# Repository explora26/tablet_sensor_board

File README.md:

# LIS3DH 三軸加速度計小板（NanoPC-T4 I2C2）

> 另一塊平板電源鍵小板在 [`power_button/`](power_button/README.md)。

板上用 LDO 轉出 3.0V，讓 I2C 電位和 NanoPC-T4 的 I2C2（3.0V I/O）一致，同時經 JST 接頭供電和 I2C 給 BQ25798 充電板。

**狀態：原理圖和 layout 完成（87.6 × 25.4 mm，雙層板），DRC 無錯誤。**

## 規格
| 項目 | 內容 |
|---|---|
| 感測器 | ST LIS3DH，LGA-16 3×3 mm |
| I2C 位址 | 0x18（SA0 接 GND），WHO_AM_I = 0x33 |
| 電源 | VIN 3.3–5.5V → TLV75530（3.0V，500 mA） |
| 上拉電阻 | SCL/SDA 各 4.7k 上拉到 3.0V（R1/R2，T4 的上拉夠用時可以不焊） |
| 介面 | J1：1×7 排針，2.54 mm，接 T4；J2：JST PH 2.0 5 pin，接 BQ25798 充電板；J3：1×10 排母，插 WL-125 RFID 模組；J4：Molex PicoBlade 1.25 mm 2 pin，接 RFID 天線 |
| 固定 | H1、H2：2 個 M3 鎖孔（3.2 mm，不鍍銅），layout 時靠近 LIS3DH 擺放，讓加速度計鎖緊固定 |

## J1 ↔ NanoPC-T4 40-pin
| J1 | 訊號 | T4 腳位 |
|---|---|---|
| 1 | VIN | Pin 2（5V） |
| 2 | GND | Pin 6 |
| 3 | SCL | Pin 5（I2C2_SCL） |
| 4 | SDA | Pin 3（I2C2_SDA） |
| 5 | INT1 | Pin 11（GPIO1_A1，3V，選用） |
| 6 | CHG_INT | Pin 7（GPIO1_A0，3V） |
| 7 | RFID_TX | Pin 21（UART4_RX，3V），需在 device tree 啟用 UART4、關閉 SPI1 |

## J2 ↔ BQ25798 充電板（JST PH 2.0，5 pin）
| J2 | 訊號 | 說明 |
|---|---|---|
| 1 | GND | |
| 2 | INT | BQ25798 的 /INT（開汲極，低電位觸發），上拉電阻在充電板上（小板不另加），經 J1 第 6 腳送到 T4 |
| 3 | I2C_SCL | 和 T4 的 I2C2 共用匯流排 |
| 4 | I2C_SDA | 同上 |
| 5 | 3V | 小板輸出的 3.0V（來自 U1），供充電板的上拉電阻和邏輯電路使用 |

I2C2 上的位址：LIS3DH 是 0x18，BQ25798 是 0x6B，沒有衝突。

## J3 ↔ WL-125 125kHz RFID 模組（1×10 排母，2.54 mm）
模組焊 10P 排針直接插上，排針從模組元件面（有 IC 的那面）焊接。模組只有 9 支腳，多出來的防呆腳在**模組第 1 腳旁邊**，所以 J3 腳位 = 模組腳位 + 1。

| J3 | 模組腳位 | 小板上的接法 |
|---|---|---|
| 1 | — | 防呆腳，不接 |
| 2 | 1 天線 1 | ANT1 → J4 第 1 腳（天線線圈），有 50–100 Vpp 諧振電壓 |
| 3 | 2 天線 2 | ANT2 → J4 第 2 腳 |
| 4 | 3 輸出模式選擇 | 接 VCC_RF（高電位 = UART 輸出，規格書規定不可懸空） |
| 5 | 4 蜂鳴器輸出 | 不接 |
| 6 | 5 TX（9600 8N1，5V TTL） | 經 Q1 BSS138 電位轉換成 3.0V（RFID_TX），送到 J1 第 7 腳 |
| 7 | 6 維根 D0 | 不接 |
| 8 | 7 /RESET（低電位有效） | R7 10k 上拉到 VCC_RF |
| 9 | 8 GND | GND |
| 10 | 9 VCC（5V） | VCC_RF：+5V 經三階 RC 濾波（見下方） |

- 電源濾波（三階 RC，依 WL-125 規格書附錄）：
  `+5V → R6 4.7Ω → C5 1000µF → R8 1Ω → C7 1000µF → R9 1Ω → C8 1000µF + C6 100nF → VCC_RF`
  - C5、C7、C8：Panasonic EEE-FT1A102AP（1000µF 10V，SMD 8 × 10.2 mm，LCSC C278408），封裝 `CP_Elec_8x10.5`；缺貨時可用 EEE-FK1A102P（C278397），但它是 10 mm，要改封裝 `CP_Elec_10x10.5`
  - R6 用 4.7Ω 限制上電湧浪電流（3000µF 從 T4 的 5V 充電，峰值約 1A）
  - 25 mA 時總壓降約 0.17V，模組約 4.8V
  - C6 補 1 MHz 以上的高頻；C8、C6 要緊貼 J3 第 10 腳
  - 1 kHz–500 kHz 約衰減 60 dB（估算值，未含走線）
- 電位轉換：Q1 BSS138 + R4/R5 各 10k 上拉（3.0V 側 / 5V 側），和 Adafruit #757 相同架構
- 卡號格式：`02` + 10 字元 ASCII 卡號 + 1 byte 校驗（XOR）+ `03`，共 13 bytes
- 規格書強調電源要乾淨：不要從 DC-DC 電感附近供電，C5 要靠近 J3
- 天線：線圈（預設 700µH）接 J4（Molex PicoBlade 53047-0210，1.25 mm 2 pin 直立），經小板走線到 J3 第 2、3 腳
- Layout 注意：ANT1/ANT2 走線（J4 ↔ J3 第 2、3 腳）有 50–100 Vpp
  - 兩條線短、平行、等長，盡量靠近，降低對外輻射和寄生電容
  - 與其他走線和鋪銅間距至少 0.5 mm，兩條線底下和周圍不要鋪銅（多餘的對地電容會讓諧振點偏移、讀卡距離變短）
  - 線圈本身遠離金屬和大面積鋪銅

> 不要接 27、28 腳：那組 I2C2 是 1.8V。完整腳位見 `docs/nanopc-t4_40pin.md`。

## 檔案
- `lis3dh_board.kicad_pro`、`lis3dh_board.kicad_sch`、`lis3dh_board.kicad_pcb`：KiCad 專案（PCB 為 KiCad 10 格式）
- `fab/lis3dh_board_gerbers.zip`：Gerber 和鑽孔檔（`fab/gerbers/` 為解開的檔案）
- `fab/bom.csv`：完整 BOM（廠牌、MPN、LCSC 料號、組裝方式、確認狀態）；電阻和陶瓷電容用國巨（YAGEO），C4 例外用 Samsung CL10A106KP8NNNC（JLC 基礎料）
- `fab/jlc_bom.csv`、`fab/jlc_cpl.csv`：JLCPCB SMT 代焊用的 BOM 和座標檔（只含 SMD 零件；J1–J4 插件手焊）
- `fab/positions.csv`：KiCad 原始座標檔
- `docs/schematic.pdf`、`docs/pcb_front.png`：原理圖 PDF 和 PCB 正面預覽
- `docs/nanopc-t4_40pin.md`：NanoPC-T4 40-pin 腳位表和接線注意事項
- `software/lis3dh_test.py`：在 T4 上讀取 X/Y/Z 的測試程式
- `scripts/gen_sch.py`：產生原理圖的腳本
- `scripts/route.sh`、`scripts/route_pcb.py`：自動佈線流程（KiCad 10 Docker + Freerouting 1.9）

## Layout
- 板子 87.6 × 25.4 mm，雙層；零件擺放和最終走線為手動調整（初版由 Freerouting 自動佈線）
- B.Cu 整面 GND；F.Cu 空白處鋪 GND，另加 6 顆 GND 縫合過孔
- 網路類別（定義在 `.kicad_pro`）：

| 類別 | 網路 | 線寬 | 間距 |
|---|---|---|---|
| Default | 訊號、+3V0、GND | 0.25 mm | 0.13 mm |
| Power | +5V、VRF1、VRF2、VCC_RF | 0.4 mm | 0.15 mm |
| ANT | ANT1、ANT2（天線，50–100 Vpp） | 0.3 mm | 0.4 mm |

- +3V0 和 GND 用 0.25 mm，因為要接進 LIS3DH 0.5 mm 腳距的焊墊；這兩個網路電流都很小
- ANT 間距 0.4 mm：PicoBlade 兩腳本身只有 0.45 mm，走線上有防焊漆覆蓋，100 Vpp 在 IPC-2221 塗覆走線的範圍內
- 過孔 0.6/0.3 mm，在 JLCPCB 標準製程範圍內

重新佈線（會清掉現有走線，零件位置不動）：
```bash
scripts/route.sh /path/to/freerouting-1.9.0.jar
```

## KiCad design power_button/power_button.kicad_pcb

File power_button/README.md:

# 平板電源鍵小板

KRHRO K6-6277D-02 直角 LED 輕觸開關（紅光）、LED 限流電阻、JST PH 2.0 4P 接頭和一個 M3 鎖孔。

**狀態：原理圖、layout、3D 模型完成（16 × 25 mm，雙層板）；KiCad 10 ERC / DRC 無錯誤。**

## J1（JST PH 2.0，4P）
| J1 | 訊號 | 說明 |
|---|---|---|
| 1 | VCC | 5V，LED 電源（經 R1 1k 到 LED 正極） |
| 2 | SW | 按下時接到 GND；上拉電阻放在主板 |
| 3 | LED_CTRL | LED 負極；主板拉到 GND 時 LED 亮 |
| 4 | GND | |

- LED 電流：(5V − 紅光約 2V) / 1k ≈ 3 mA
- LED_CTRL 會被 LED 拉到接近 5V − Vf，**不可直接接 3V GPIO**；主板請用 NPN / N-MOSFET 或開汲極輸出控制，要常亮就直接接 GND
- 開關額定 DC 30V 0.3A

## 機構重點
- 按鍵中心離板面 3.80 mm，按鍵帽 Ø8.30 × 2.50 mm，帽子底部比板面低 0.35 mm，所以**按鍵帽必須伸出板邊**
- 板子下緣在第 4 腳往前 4.58 mm（本體前緣附近），頸部和按鍵帽伸出板外；按鍵帽後緣在第 4 腳往前 6.7 mm、帽面 9.2 mm
- 本體外框：寬 7.6 mm，第 4 腳往後 4.05 mm 到往前 4.7 mm，高 7.4 mm
- H1：M3 鎖孔（3.2 mm，不鍍銅）
- `3d/power_button_board.step`：整片板子含零件的 STEP，可直接匯入機構軟體
- `3d/KRHRO_K6-6277D.step`：開關的簡化模型（依 KRHRO 圖面尺寸建立，外形包絡正確，內部細節省略）

## 檔案
- `power_button.kicad_pro / .kicad_sch / .kicad_pcb`：KiCad 專案；`fp-lib-table` 指到專案內的 `power_button.pretty`
- `power_button.pretty/KRHRO_K6-6277D.kicad_mod`：開關封裝（依圖面 PCB Layout 繪製，已掛 3D 模型）
- `fab/power_button_gerbers.zip`、`fab/positions.csv`、`fab/bom.csv`：製造檔
- `docs/schematic.pdf`、`docs/pcb_3d_top.png`、`docs/pcb_3d_iso.png`
- `scripts/gen_sch.py`、`scripts/gen_pcb.py`、`scripts/gen_3d.py`：產生原理圖、PCB（Freerouting 佈線）和 3D 模型的腳本

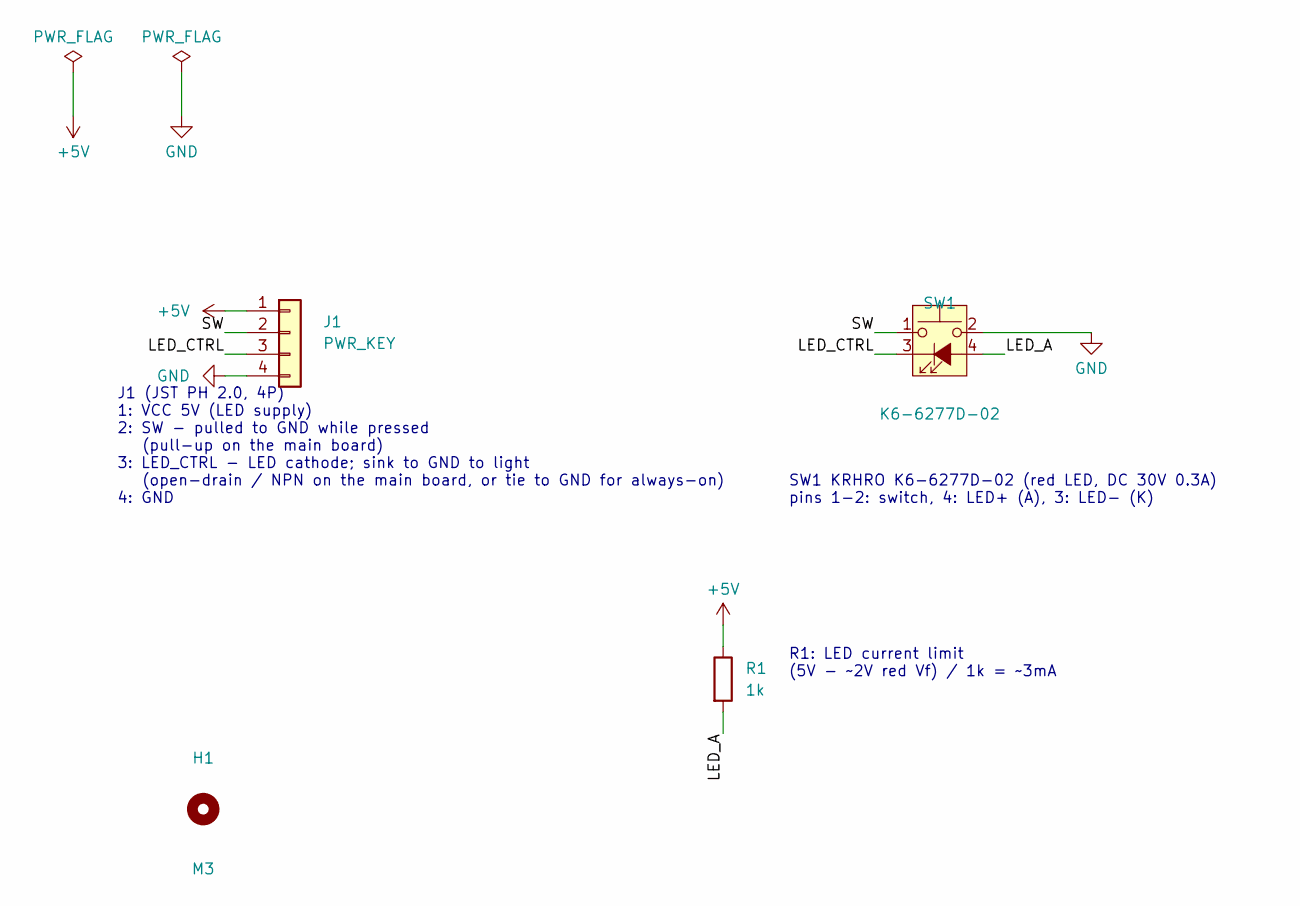
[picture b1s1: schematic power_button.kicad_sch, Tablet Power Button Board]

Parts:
H1: M3; MountingHole_3.2mm_M3
J1: PWR_KEY; JST_PH_B4B-PH-K_1x04_P2.00mm_Vertical; MPN JST B4B-PH-K-S(LF)(SN)
R1: 1k; R_0603_1608Metric; MPN YAGEO RC0603FR-071KL
SW1: K6-6277D-02; KRHRO_K6-6277D; MPN KRHRO K6-6277D-02; LCSC C693836

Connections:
+5V: J1.1, R1.1
/LED_A: R1.2, SW1.4 (A)
/LED_CTRL: J1.3, SW1.3 (K)
/SW: J1.2, SW1.1
GND: J1.4, SW1.2

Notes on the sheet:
J1 (JST PH 2.0, 4P) 1: VCC 5V (LED supply) 2: SW - pulled to GND while pressed (pull-up on the main board) 3: LED_CTRL - LED cathode; sink to GND to light (open-drain / NPN on the main board, or tie to GND for always-on) 4: GND
SW1 KRHRO K6-6277D-02 (red LED, DC 30V 0.3A) pins 1-2: switch, 4: LED+ (A), 3: LED- (K)
R1: LED current limit (5V - ~2V red Vf) / 1k = ~3mA

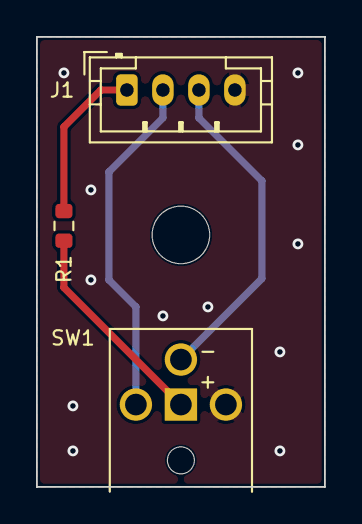
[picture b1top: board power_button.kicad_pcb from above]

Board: 2 copper layers, 16.0 x 25.0 mm, 4 parts (0 on the bottom side), 5 nets.

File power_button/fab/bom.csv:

Designator,Qty,Value,Package,Manufacturer,MPN,LCSC,Assembly,Status,Notes
SW1,1,K6-6277D-02 (red LED),THT right-angle,KRHRO,K6-6277D-02,C693836,hand solder,check,LCSC number from the datasheet file name; confirm it is the red (-02) variant
R1,1,1k 1%,0603,YAGEO,RC0603FR-071KL,,SMT or hand solder,find LCSC,LED current limit (~3mA at 5V)
J1,1,JST PH 4P vertical,2.0mm THT,JST,B4B-PH-K-S(LF)(SN),,hand solder,find LCSC,Main board connection

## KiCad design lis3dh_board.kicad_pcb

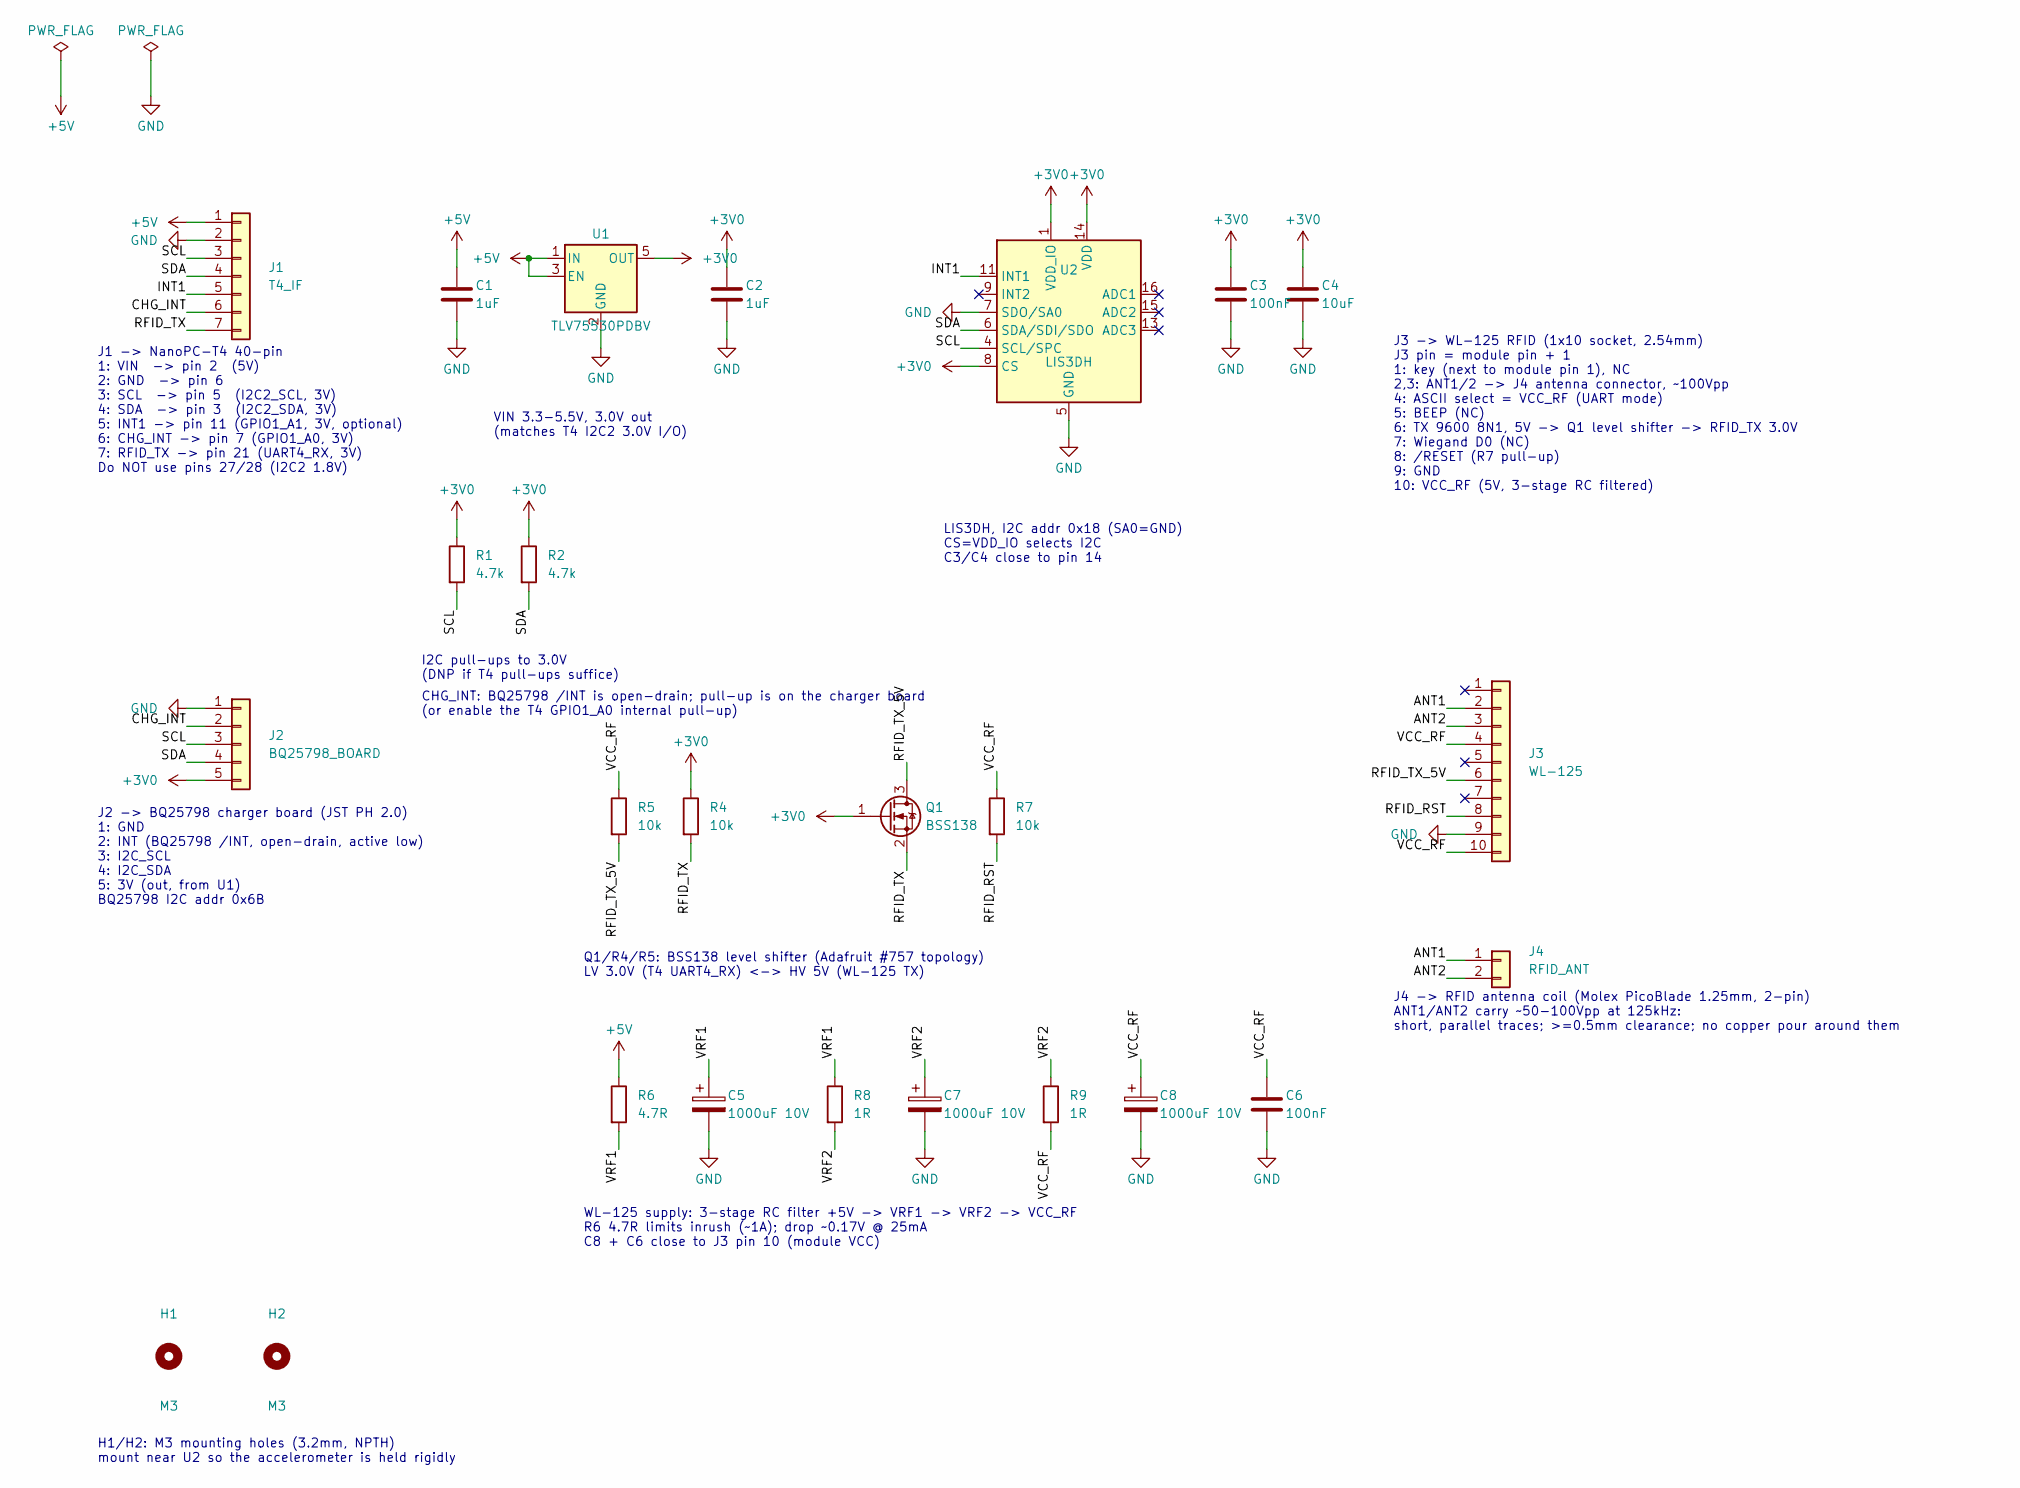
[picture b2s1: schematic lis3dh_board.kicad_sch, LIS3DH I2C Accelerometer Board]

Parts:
C1, C2: 1uF; C_0603_1608Metric
C3, C6: 100nF; C_0603_1608Metric
C4: 10uF; C_0603_1608Metric
C5, C7, C8: 1000uF 10V; CP_Elec_8x10.5; MPN Panasonic EEE-FT1A102AP; LCSC C278408
H1, H2: M3; MountingHole_3.2mm_M3
J1: T4_IF; PinHeader_1x07_P2.54mm_Vertical
J2: BQ25798_BOARD; JST_PH_B5B-PH-K_1x05_P2.00mm_Vertical
J3: WL-125; PinSocket_1x10_P2.54mm_Vertical
J4: RFID_ANT; Molex_PicoBlade_53047-0210_1x02_P1.25mm_Vertical; MPN Molex 53047-0210
Q1: BSS138; SOT-23
R1, R2: 4.7k; R_0603_1608Metric
R4, R5, R7: 10k; R_0603_1608Metric
R6: 4.7R; R_0805_2012Metric
R8, R9: 1R; R_0805_2012Metric
U1: TLV75530PDBV; SOT-23-5
U2: LIS3DH; LGA-16_3x3mm_P0.5mm_LayoutBorder3x5y

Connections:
+3V0: C2.1, C3.1, C4.1, J2.5, Q1.1 (G), R1.1, R2.1, R4.1, U1.5 (OUT), U2.1 (VDD_IO), U2.8 (CS), U2.14 (VDD)
+5V: C1.1, J1.1, R6.1, U1.1 (IN), U1.3 (EN)
/ANT1: J3.2, J4.1
/ANT2: J3.3, J4.2
/CHG_INT: J1.6, J2.2
/INT1: J1.5, U2.11 (INT1)
/RFID_RST: J3.8, R7.2
/RFID_TX: J1.7, Q1.2 (S), R4.2
/RFID_TX_5V: J3.6, Q1.3 (D), R5.2
/SCL: J1.3, J2.3, R1.2, U2.4 (SCL/SPC)
/SDA: J1.4, J2.4, R2.2, U2.6 (SDA/SDI/SDO)
/VCC_RF: C6.1, C8.1, J3.4, J3.10, R5.1, R7.1, R9.2
/VRF1: C5.1, R6.2, R8.1
/VRF2: C7.1, R8.2, R9.1
GND: C1.2, C2.2, C3.2, C4.2, C5.2, C6.2, C7.2, C8.2, J1.2, J2.1, J3.9, U1.2 (GND), U2.5 (GND), U2.7 (SDO/SA0), U2.10 (GND), U2.12 (GND)

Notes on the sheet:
J1 -> NanoPC-T4 40-pin 1: VIN -> pin 2 (5V) 2: GND -> pin 6 3: SCL -> pin 5 (I2C2_SCL, 3V) 4: SDA -> pin 3 (I2C2_SDA, 3V) 5: INT1 -> pin 11 (GPIO1_A1, 3V, optional) 6: CHG_INT -> pin 7 (GPIO1_A0, 3V) 7: RFID_TX -> pin 21 (UART4_RX, 3V) Do NOT use pins 27/28 (I2C2 1.8V)
VIN 3.3-5.5V, 3.0V out (matches T4 I2C2 3.0V I/O)
I2C pull-ups to 3.0V (DNP if T4 pull-ups suffice)
J2 -> BQ25798 charger board (JST PH 2.0) 1: GND 2: INT (BQ25798 /INT, open-drain, active low) 3: I2C_SCL 4: I2C_SDA 5: 3V (out, from U1) BQ25798 I2C addr 0x6B
CHG_INT: BQ25798 /INT is open-drain; pull-up is on the charger board (or enable the T4 GPIO1_A0 internal pull-up)
J3 -> WL-125 RFID (1x10 socket, 2.54mm) J3 pin = module pin + 1 1: key (next to module pin 1), NC 2,3: ANT1/2 -> J4 antenna connector, ~100Vpp 4: ASCII select = VCC_RF (UART mode) 5: BEEP (NC) 6: TX 9600 8N1, 5V -> Q1 level shifter -> RFID_TX 3.0V 7: Wiegand D0 (NC) 8: /RESET (R7 pull-up) 9: GND 10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
J4 -> RFID antenna coil (Molex PicoBlade 1.25mm, 2-pin) ANT1/ANT2 carry ~50-100Vpp at 125kHz: short, parallel traces; >=0.5mm clearance; no copper pour around them
Q1/R4/R5: BSS138 level shifter (Adafruit #757 topology) LV 3.0V (T4 UART4_RX) <-> HV 5V (WL-125 TX)
WL-125 supply: 3-stage RC filter +5V -> VRF1 -> VRF2 -> VCC_RF R6 4.7R limits inrush (~1A); drop ~0.17V @ 25mA C8 + C6 close to J3 pin 10 (module VCC)
LIS3DH, I2C addr 0x18 (SA0=GND) CS=VDD_IO selects I2C C3/C4 close to pin 14
H1/H2: M3 mounting holes (3.2mm, NPTH) mount near U2 so the accelerometer is held rigidly

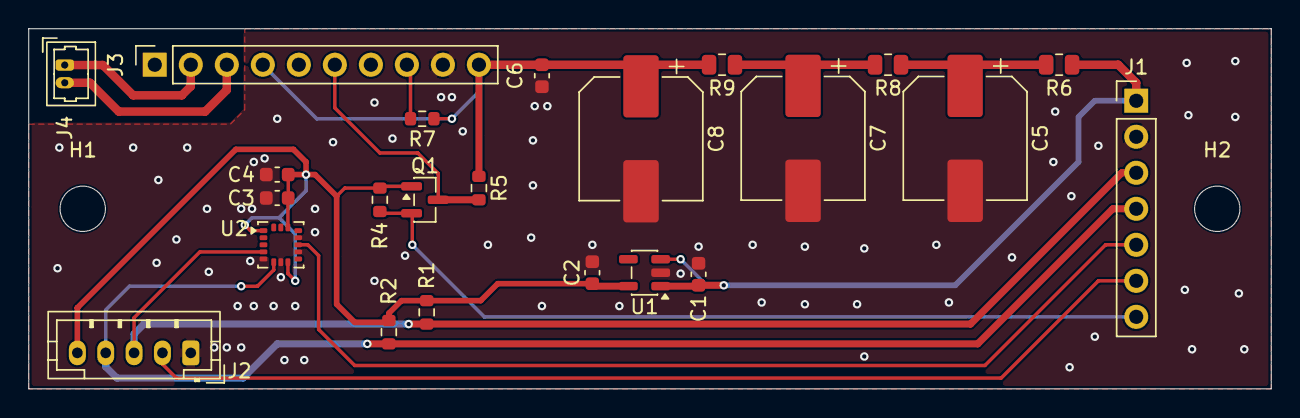
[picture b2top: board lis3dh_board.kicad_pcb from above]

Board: 2 copper layers, 87.6 x 25.4 mm, 25 parts (0 on the bottom side), 15 nets.

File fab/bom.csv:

Designator,Qty,Value,Footprint,Description
U2,1,LIS3DH,LGA-16 3x3mm P0.5mm,ST 3-axis accelerometer (I2C addr 0x18)
U1,1,TLV75530PDBV,SOT-23-5,TI 500mA LDO fixed 3.0V
C1 C2,2,1uF 10V X7R,0603,LDO input/output capacitors
C3,1,100nF 10V X7R,0603,LIS3DH VDD decoupling
C4,1,10uF 6.3V X5R,0603,LIS3DH bulk decoupling
R1 R2,2,4.7k 1%,0603,I2C pull-ups to 3.0V (optional)
J1,1,1x07 pin header,2.54mm vertical,Connection to NanoPC-T4
J2,1,JST PH B5B-PH-K,2.0mm vertical,Connection to BQ25798 charger board
J3,1,1x10 pin socket,2.54mm vertical,Socket for WL-125 RFID module (pin 1 = key, J3 pin = module pin + 1)
J4,1,Molex PicoBlade 53047-0210,1.25mm 2-pin vertical THT,RFID antenna coil connector
Q1,1,BSS138,SOT-23,RFID TX level shifter 5V -> 3.0V
R4,1,10k 1%,0603,Level shifter LV-side pull-up (3.0V)
R5,1,10k 1%,0603,Level shifter HV-side pull-up (VCC_RF 5V)
R6,1,4.7R,0805,RFID supply RC filter stage 1 (limits inrush)
R8 R9,2,1R,0805,RFID supply RC filter stages 2-3
R7,1,10k 1%,0603,WL-125 /RESET pull-up
C5 C7 C8,3,1000uF 10V,SMD 8x10.2mm (CP_Elec_8x10.5),RFID supply RC filter capacitors - Panasonic EEE-FT1A102AP (LCSC C278408)
C6,1,100nF 10V X7R,0603,RFID supply HF decoupling (at J3)

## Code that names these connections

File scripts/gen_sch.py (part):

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pwr(j1['2'], 'GND')
label(j1['3'], 'SCL')
label(j1['4'], 'SDA')
label(j1['5'], 'INT1')
label(j1['6'], 'CHG_INT')
label(j1['7'], 'RFID_TX')
text('J1 -> NanoPC-T4 40-pin\n1: VIN  -> pin 2  (5V)\n2: GND  -> pin 6\n'
     '3: SCL  -> pin 5  (I2C2_SCL, 3V)\n4: SDA  -> pin 3  (I2C2_SDA, 3V)\n5: INT1 -> pin 11 (GPIO1_A1, 3V, optional)\n6: CHG_INT -> pin 7 (GPIO1_A0, 3V)\n7: RFID_TX -> pin 21 (UART4_RX, 3V)\nDo NOT use pins 27/28 (I2C2 1.8V)',
     30.48, 104.14)

# power flags: +5V and GND come only from the connector
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j2 = place('Connector_Generic:Conn_01x05', 'J2', 'BQ25798_BOARD', 50.8, 142.24,
           footprint='Connector_JST:JST_PH_B5B-PH-K_1x05_P2.00mm_Vertical')
pwr(j2['1'], 'GND')
label(j2['2'], 'CHG_INT')
label(j2['3'], 'SCL')
label(j2['4'], 'SDA')
pwr(j2['5'], '+3V0')     # 3.0V supplied to the charger board (pull-ups / logic)
text('J2 -> BQ25798 charger board (JST PH 2.0)\n1: GND\n2: INT (BQ25798 /INT, open-drain, active low)\n'
     '3: I2C_SCL\n4: I2C_SDA\n5: 3V (out, from U1)\nBQ25798 I2C addr 0x6B', 30.48, 165.1)
text('CHG_INT: BQ25798 /INT is open-drain; pull-up is on the charger board\n(or enable the T4 GPIO1_A0 internal pull-up)', 76.2, 138.43)

# ---- J3: WL-125 125kHz RFID module (plugs in, 1x10 socket) ----------------------
# J3 pin 1 is the polarization key (next to module pin 1); module pins 1-9 map to J3 2-10.
j3 = place('Connector_Generic:Conn_01x10', 'J3', 'WL-125', 228.6, 144.78,
           footprint='Connector_PinSocket_2.54mm:PinSocket_1x10_P2.54mm_Vertical')
nc(j3['1'])                   # key
label(j3['2'], 'ANT1')        # module 1 ANT1: ~100 Vpp resonant voltage
label(j3['3'], 'ANT2')        # module 2 ANT2
label(j3['4'], 'VCC_RF')      # module 3 ASCII select: high = UART output (must not float)
nc(j3['5'])                   # module 4 BEEP
label(j3['6'], 'RFID_TX_5V')  # module 5 TX 9600 8N1, 5V TTL
nc(j3['7'])                   # module 6 Wiegand D0
label(j3['8'], 'RFID_RST')    # module 7 /RESET, active low
pwr(j3['9'], 'GND')           # module 8 GND
label(j3['10'], 'VCC_RF')     # module 9 VCC
text('J3 -> WL-125 RFID (1x10 socket, 2.54mm)\n'
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j4 = place('Connector_Generic:Conn_01x02', 'J4', 'RFID_ANT', 228.6, 172.72,
           footprint='Connector_Molex:Molex_PicoBlade_53047-0210_1x02_P1.25mm_Vertical',
           fields={'MPN': 'Molex 53047-0210'})
label(j4['1'], 'ANT1')
label(j4['2'], 'ANT2')
text('J4 -> RFID antenna coil (Molex PicoBlade 1.25mm, 2-pin)\n'
     'ANT1/ANT2 carry ~50-100Vpp at 125kHz:\n'
     'short, parallel traces; >=0.5mm clearance; no copper pour around them',
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# (same topology as Adafruit #757), LV side 3.0V, HV side VCC_RF
r5 = place('Device:R', 'R5', '10k', 104.14, 152.4, footprint=R_FP)
label(r5['1'], 'VCC_RF')
label(r5['2'], 'RFID_TX_5V')
r4 = place('Device:R', 'R4', '10k', 114.3, 152.4, footprint=R_FP)
pwr(r4['1'], '+3V0')
label(r4['2'], 'RFID_TX')
q1 = place('Transistor_FET:BSS138', 'Q1', 'BSS138', 142.24, 152.4,
           footprint='Package_TO_SOT_SMD:SOT-23',
           rpos=(147.32, 151.13), rjust='left', vpos=(147.32, 153.67), vjust='left')
pwr(q1['1'], '+3V0')          # G -> LV supply
label(q1['2'], 'RFID_TX')     # S -> LV side (T4)
label(q1['3'], 'RFID_TX_5V')  # D -> HV side (WL-125 TX)
text('Q1/R4/R5: BSS138 level shifter (Adafruit #757 topology)\n'
     'LV 3.0V (T4 UART4_RX) <-> HV 5V (WL-125 TX)', 99.06, 175.26)
r7 = place('Device:R', 'R7', '10k', 157.48, 152.4, footprint=R_FP)
label(r7['1'], 'VCC_RF')
label(r7['2'], 'RFID_RST')

# clean 5V for the 125kHz reader: 3-stage RC (per WL-125 datasheet appendix).
# First R is 4.7R to limit inrush into 3 x 1000uF from the T4 5V pin (~1A peak);
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RF_C = 'Capacitor_SMD:CP_Elec_8x10.5'
r6 = place('Device:R', 'R6', '4.7R', 104.14, 193.04, footprint=RF_R)
pwr(r6['1'], '+5V')
label(r6['2'], 'VRF1')
c5 = place('Device:C_Polarized', 'C5', '1000uF 10V', 116.84, 193.04, footprint=RF_C,
           fields={'MPN': 'Panasonic EEE-FT1A102AP', 'LCSC': 'C278408'})
label(c5['1'], 'VRF1')
pwr(c5['2'], 'GND')
r8 = place('Device:R', 'R8', '1R', 134.62, 193.04, footprint=RF_R)
label(r8['1'], 'VRF1')
label(r8['2'], 'VRF2')
c7 = place('Device:C_Polarized', 'C7', '1000uF 10V', 147.32, 193.04, footprint=RF_C,
           fields={'MPN': 'Panasonic EEE-FT1A102AP', 'LCSC': 'C278408'})
label(c7['1'], 'VRF2')
pwr(c7['2'], 'GND')
r9 = place('Device:R', 'R9', '1R', 165.1, 193.04, footprint=RF_R)
label(r9['1'], 'VRF2')
label(r9['2'], 'VCC_RF')
c8 = place('Device:C_Polarized', 'C8', '1000uF 10V', 177.8, 193.04, footprint=RF_C,
           fields={'MPN': 'Panasonic EEE-FT1A102AP', 'LCSC': 'C278408'})
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label(u2['6'], 'SDA')
pwr(u2['7'], 'GND')     # SA0 = 0 -> address 0x18
pwr(u2['8'], '+3V0')    # CS high -> I2C mode
label(u2['11'], 'INT1')
nc(u2['9'])             # INT2
for p in ('13', '15', '16'):
    nc(u2[p])           # ADC1..3 unused
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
